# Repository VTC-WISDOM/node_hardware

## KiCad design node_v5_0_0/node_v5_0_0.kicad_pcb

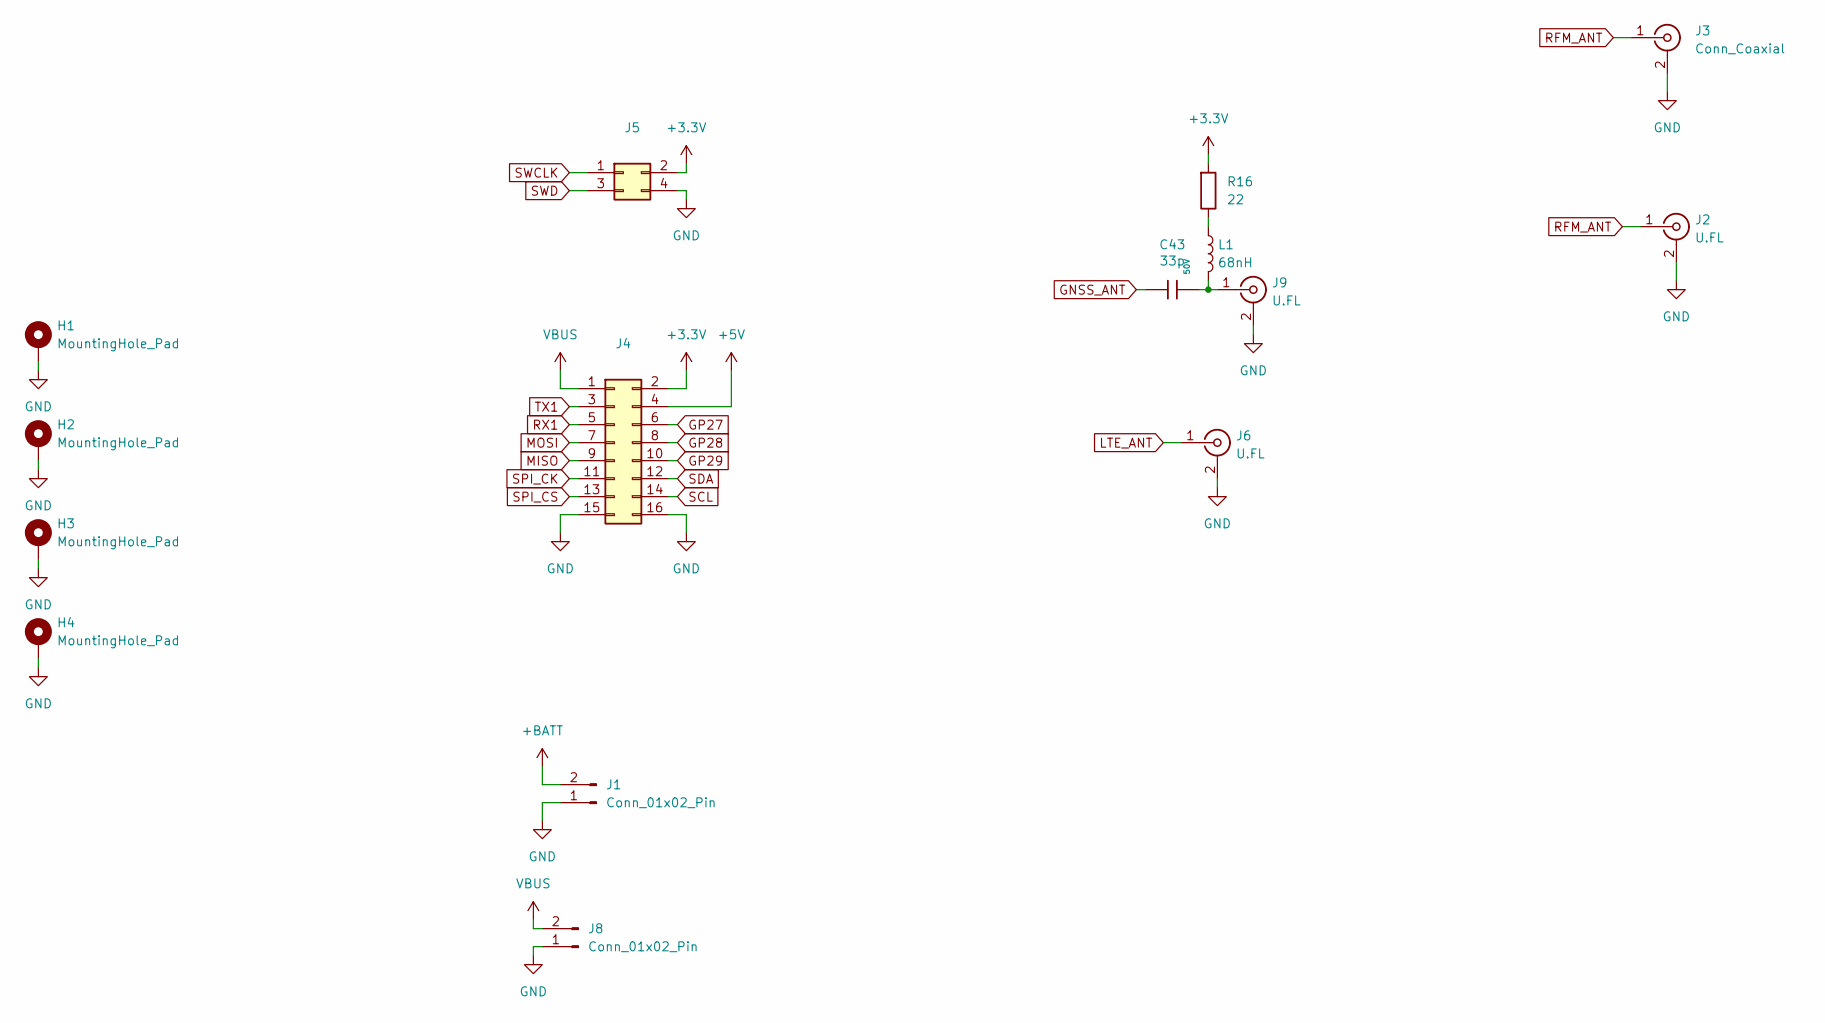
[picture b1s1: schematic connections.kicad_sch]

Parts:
C43: 33p; C_0402; Voltage Rated 50V; Tolerance ±5%; Part 0402CG330J500NT; LCSC C1562
H1, H2, H3, H4: MountingHole_Pad; MountingHole_2.2mm_M2_Pad_TopBottom
J1, J8: Conn_01x02_Pin; JST_PH_B2B-PH-K_1x02_P2.00mm_Vertical
J2, J6, J9: U.FL; IPEX-SMD_BWIPX-1-001E; LCSC C5137195
J3: Conn_Coaxial; SMA_Samtec_SMA-J-P-H-ST-EM1_EdgeMount
J4: Conn_02x08_Odd_Even; PinHeader_2x08_P2.54mm_Vertical
J5: Conn_02x02_Odd_Even; PinHeader_2x02_P2.54mm_Vertical
L1: 68nH; L_0402_1005Metric_Pad0.77x0.64mm_HandSolder
R16: 22; R_0805; Overload Voltage (Max) 150V; Tolerance ±1%; Part 0805W8F220JT5E; LCSC C17561

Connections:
+3.3V: J4.2, J5.2, R16.1; also elsewhere on the board
+5V: J4.4; also elsewhere on the board
+BATT: J1.2; also elsewhere on the board
GND: H1.1, H2.1, H3.1, H4.1, J1.1, J2.2 (Ext), J2.3, J3.2 (Ext), J4.15, J4.16, J5.4, J6.2 (Ext), J6.3, J8.1, J9.2 (Ext), J9.3; also elsewhere on the board
GNSS_ANT: C43.1; also elsewhere on the board
GP27: J4.6; also elsewhere on the board
GP28: J4.8; also elsewhere on the board
GP29: J4.10; also elsewhere on the board
LTE_ANT: J6.1 (In); also elsewhere on the board
MISO: J4.9; also elsewhere on the board
MOSI: J4.7; also elsewhere on the board
unnamed: C43.2, J9.1 (In), L1.2
unnamed: L1.1, R16.2
RFM_ANT: J2.1 (In), J3.1 (In); also elsewhere on the board
RX1: J4.5; also elsewhere on the board
SCL: J4.14; also elsewhere on the board
SDA: J4.12; also elsewhere on the board
SPI_CK: J4.11; also elsewhere on the board
SPI_CS: J4.13; also elsewhere on the board
SWCLK: J5.1; also elsewhere on the board
SWD: J5.3; also elsewhere on the board
TX1: J4.3; also elsewhere on the board
VBUS: J4.1, J8.2; also elsewhere on the board

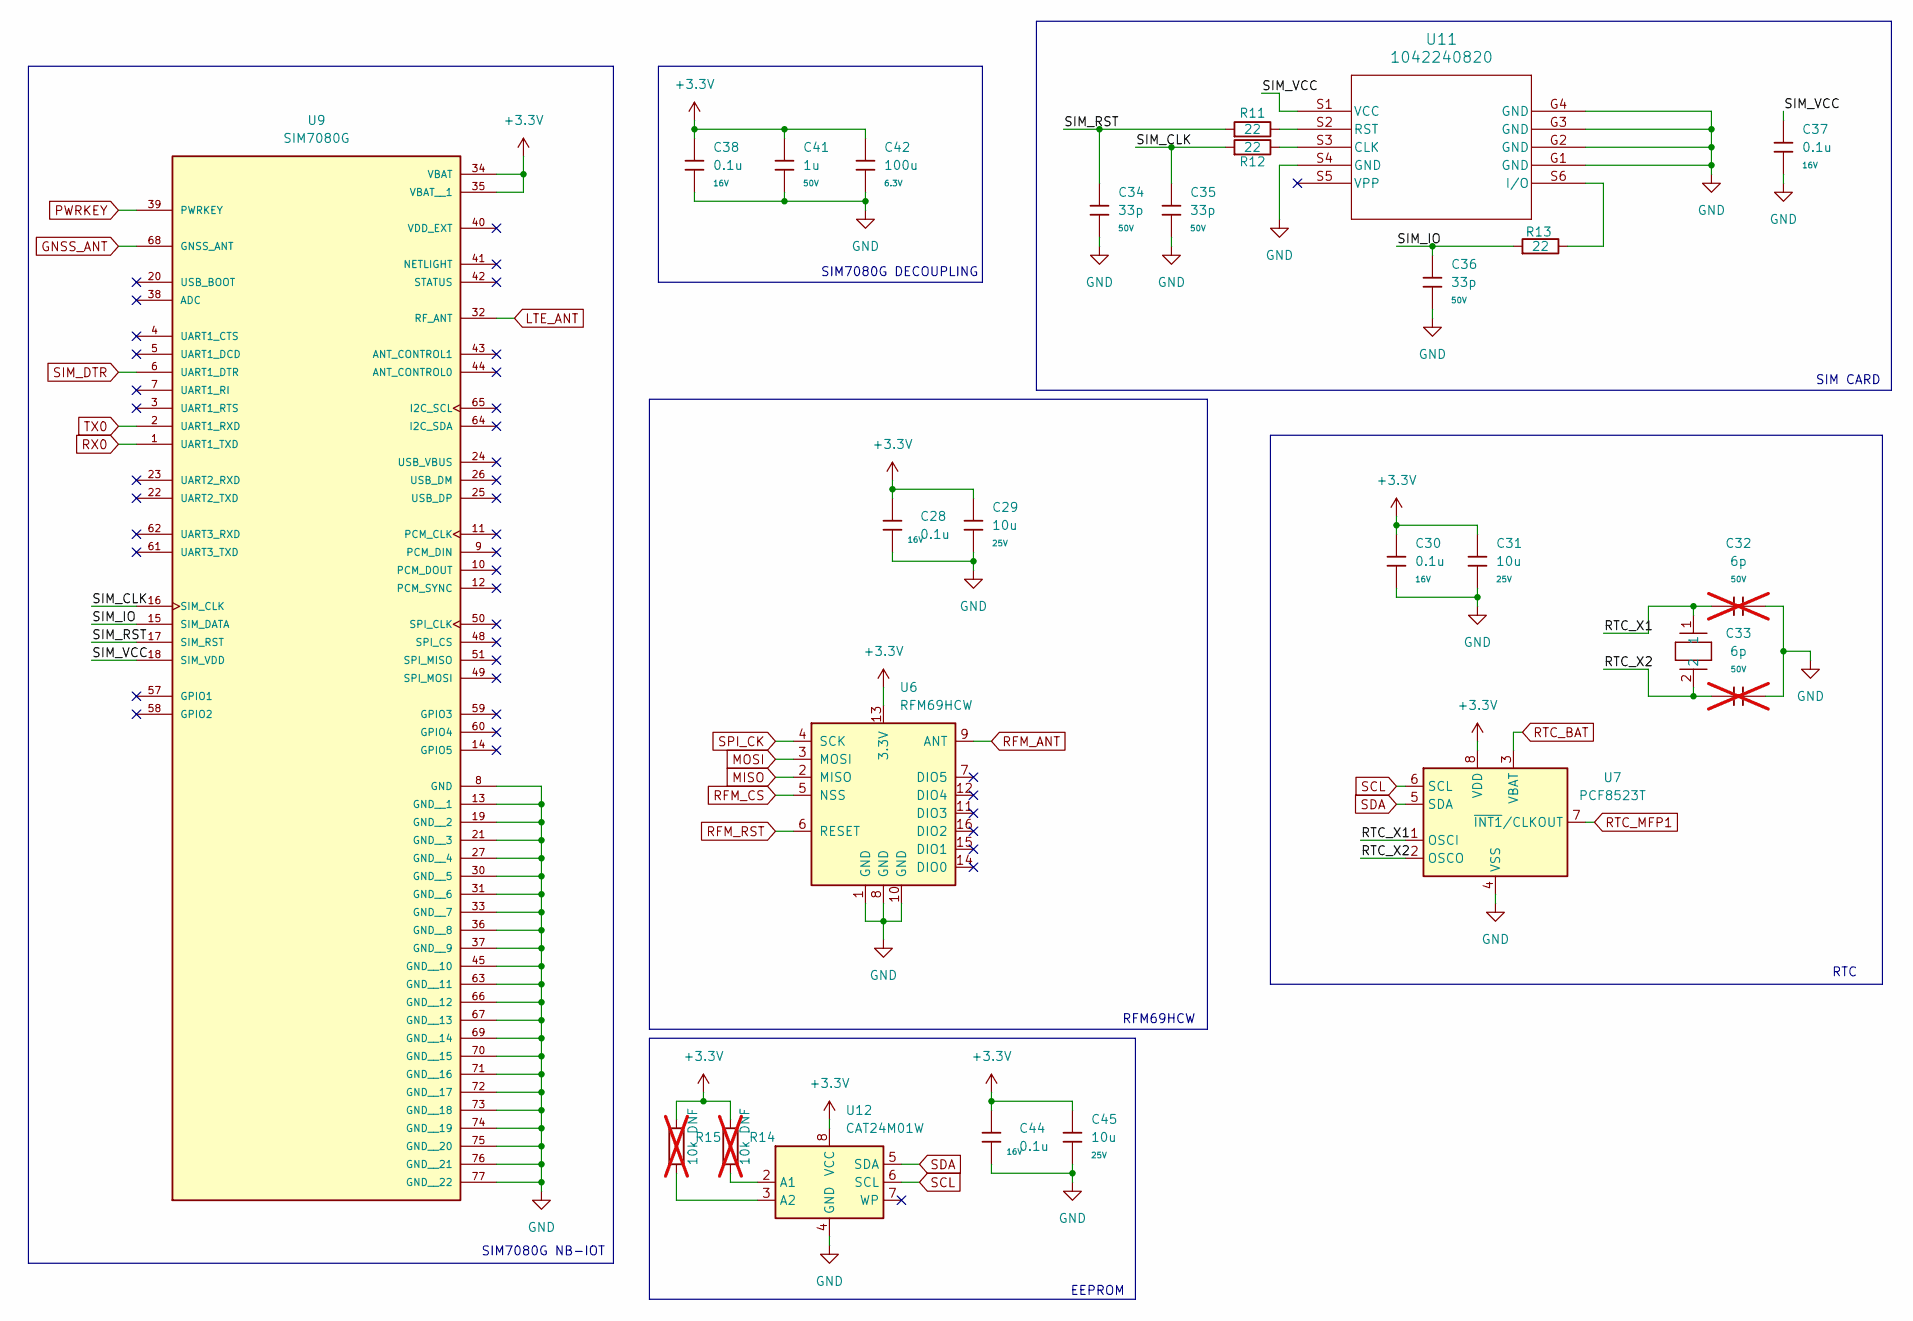
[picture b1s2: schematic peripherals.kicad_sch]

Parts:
C28, C30, C37, C38, C44: 0.1u; C_0402; Voltage Rated 16V; Tolerance ±10%; Part CL05B104KO5NNNC; LCSC C1525
C29, C31, C45: 10u; C_0805; Voltage Rated 25V; Tolerance ±10%; Part CL21A106KAYNNNE; LCSC C15850
C32, C33: 6p; C_0603; Voltage Rated 50V; Part 0603CG6R0C500NT; LCSC C37474; not fitted
C34, C35, C36: 33p; C_0402; Voltage Rated 50V; Tolerance ±5%; Part 0402CG330J500NT; LCSC C1562
C41: 1u; C_0805; Voltage Rated 50V; Tolerance ±10%; Part CL21B105KBFNNNE; LCSC C28323
C42: 100u; C_0805; Voltage Rated 6.3V; Tolerance ±20%; Part CL21A476MQYNNNE; LCSC C16780
R11, R12, R13: 22; R_0805; Overload Voltage (Max) 150V; Tolerance ±1%; Part 0805W8F220JT5E; LCSC C17561
R14, R15: 10k DNF; R_0402_1005Metric_Pad0.72x0.64mm_HandSolder; not fitted
U6: RFM69HCW; HOPERF_RFM9XW_SMD
U7: PCF8523T; SOIC-8_3.9x4.9mm_P1.27mm
U9: SIM7080G; XCVR_SIM7080G; PARTREV 1.04
U11: 1042240820; 1042240820_MOL
U12: CAT24M01W; SOIC-8_3.9x4.9mm_P1.27mm
XTAL1: SC32S-7PF20PPM; XTAL_SC32S-7PF20PPM_EPS

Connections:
+3.3V: C28.1, C29.1, C30.1, C31.1, C38.1, C41.1, C42.1, C44.1, C45.1, R14.1, R15.1, U6.13 (3.3V), U7.8 (VDD), U9.34 (VBAT), U9.35 (VBAT__1), U12.8 (VCC); also elsewhere on the board
/PERIPHERALS/RTC_X1: C32.1, U7.1 (OSCI), XTAL1.1
/PERIPHERALS/RTC_X2: C33.1, U7.2 (OSCO), XTAL1.2
/PERIPHERALS/SIM_CLK: C35.1, R12.1, U9.16 (SIM_CLK)
/PERIPHERALS/SIM_IO: C36.1, R13.1, U9.15 (SIM_DATA)
/PERIPHERALS/SIM_RST: C34.1, R11.1, U9.17 (SIM_RST)
/PERIPHERALS/SIM_VCC: C37.1, U9.18 (SIM_VDD), U11.S1 (VCC)
GND: C28.2, C29.2, C30.2, C31.2, C32.2, C33.2, C34.2, C35.2, C36.2, C37.2, C38.2, C41.2, C42.2, C44.2, C45.2, U6.1 (GND), U6.8 (GND), U6.10 (GND), U7.4 (VSS), U9.8 (GND), U9.13 (GND__1), U9.19 (GND__2), U9.21 (GND__3), U9.27 (GND__4), U9.30 (GND__5), U9.31 (GND__6), U9.33 (GND__7), U9.36 (GND__8), U9.37 (GND__9), U9.45 (GND__10), U9.63 (GND__11), U9.66 (GND__12), U9.67 (GND__13), U9.69 (GND__14), U9.70 (GND__15), U9.71 (GND__16), U9.72 (GND__17), U9.73 (GND__18), U9.74 (GND__19), U9.75 (GND__20), U9.76 (GND__21), U9.77 (GND__22), U11.11, U11.12, U11.G1 (GND), U11.G2 (GND), U11.G3 (GND), U11.G4 (GND), U11.S4 (GND), U12.4 (GND); also elsewhere on the board
GNSS_ANT: U9.68 (GNSS_ANT); also elsewhere on the board
LTE_ANT: U9.32 (RF_ANT); also elsewhere on the board
MISO: U6.2 (MISO); also elsewhere on the board
MOSI: U6.3 (MOSI); also elsewhere on the board
unnamed 34: U7.3 (VBAT); also elsewhere on the board
unnamed: R12.2, U11.S3 (CLK)
unnamed: R13.2, U11.S6 (I/O)
unnamed: R11.2, U11.S2 (RST)
unnamed: R14.2, U12.2 (A1)
unnamed: R15.2, U12.3 (A2)
PWRKEY: U9.39 (PWRKEY); also elsewhere on the board
RFM_ANT: U6.9 (ANT); also elsewhere on the board
RFM_CS: U6.5 (NSS); also elsewhere on the board
RFM_DIO0: U6.14 (DIO0); also elsewhere on the board
RFM_DIO1: U6.15 (DIO1); also elsewhere on the board
RFM_DIO2: U6.16 (DIO2); also elsewhere on the board
RFM_DIO3: U6.11 (DIO3); also elsewhere on the board
RFM_DIO4: U6.12 (DIO4); also elsewhere on the board
RFM_DIO5: U6.7 (DIO5); also elsewhere on the board
RFM_RST: U6.6 (RESET); also elsewhere on the board
RTC_MFP1: U7.7 (~INT1/CLKOUT); also elsewhere on the board
RX0: U9.1 (UART1_TXD); also elsewhere on the board
SCL: U7.6 (SCL), U12.6 (SCL); also elsewhere on the board
SDA: U7.5 (SDA), U12.5 (SDA); also elsewhere on the board
SIM_DTR: U9.6 (UART1_DTR); also elsewhere on the board
SPI_CK: U6.4 (SCK); also elsewhere on the board
TX0: U9.2 (UART1_RXD); also elsewhere on the board

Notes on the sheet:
RFM69HCW
EEPROM
SIM7080G DECOUPLING
RTC
SIM CARD
SIM7080G NB-IOT

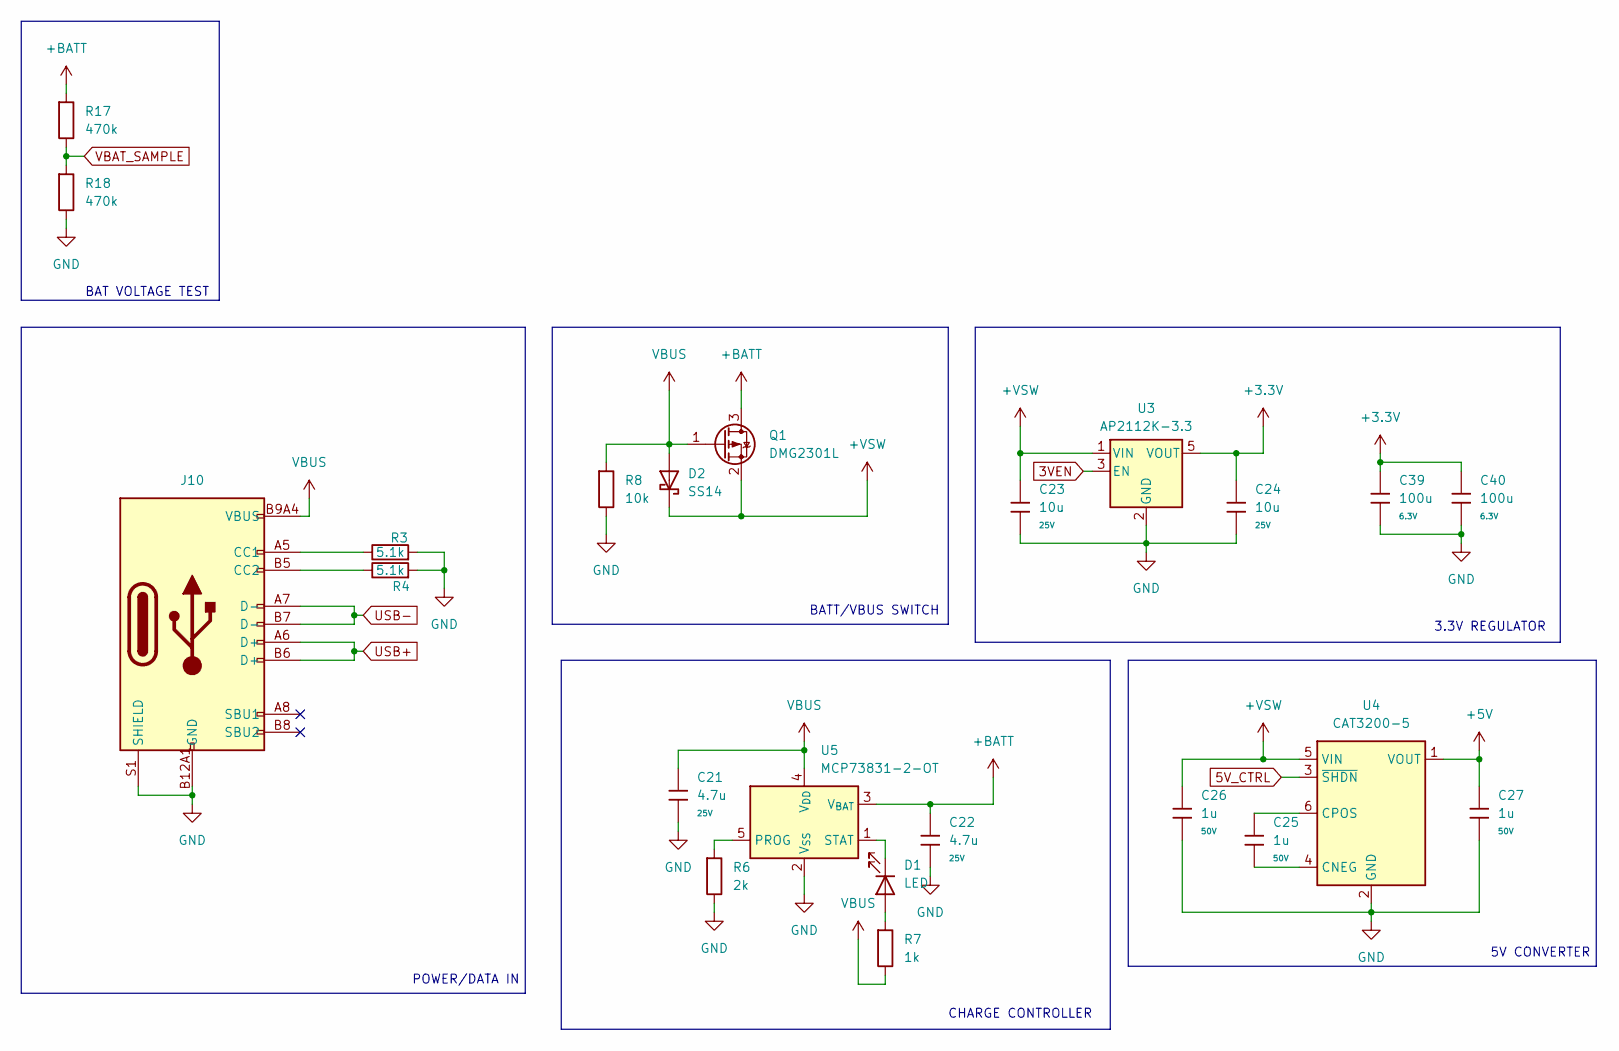
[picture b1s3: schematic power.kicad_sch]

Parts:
C21, C22: 4.7u; C_0805; Voltage Rated 25V; Tolerance ±10%; Part CL21A475KAQNNNE; LCSC C1779
C23, C24: 10u; C_0805; Voltage Rated 25V; Tolerance ±10%; Part CL21A106KAYNNNE; LCSC C15850
C25, C26, C27: 1u; C_0805; Voltage Rated 50V; Tolerance ±10%; Part CL21B105KBFNNNE; LCSC C28323
C39, C40: 100u; C_0805; Voltage Rated 6.3V; Tolerance ±20%; Part CL21A476MQYNNNE; LCSC C16780
D1: LED; LED_1206_3216Metric_Pad1.42x1.75mm_HandSolder
D2: SS14; D_SMA; Forward Voltage (Vf@If) 550mV@1A; Reverse Voltage (Vr) 40V; Part SS14; LCSC C2480
J10: Connector, USB-TYPE-C-16P; TYPE-C-SMD_HX-TYPE-C-16PIN; LCSC C2927039
Q1: DMG2301L; SOT-23
R3, R4: 5.1k; R_0805_2012Metric_Pad1.20x1.40mm_HandSolder
R6: 2k; R_0805; Overload Voltage (Max) 150V; Tolerance ±1%; Part 0805W8F2001T5E; LCSC C17604
R7: 1k; R_0805; Overload Voltage (Max) 150V; Tolerance ±1%; Part 0805W8F1001T5E; LCSC C17513
R8: 10k; R_0805; Overload Voltage (Max) 150V; Tolerance ±1%; Part 0805W8F1002T5E; LCSC C17414
R17, R18: 470k; R_0805; Overload Voltage (Max) 150V; Tolerance ±1%; Part 0805W8F4703T5E; LCSC C17709
U3: AP2112K-3.3; SOT-23-5
U4: CAT3200-5; SOT-23-6
U5: MCP73831-2-OT; SOT-23-5

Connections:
3VEN: U3.3 (EN); also elsewhere on the board
5V_CTRL: U4.3 (~SHDN); also elsewhere on the board
+3.3V: C24.1, C39.1, C40.1, U3.5 (VOUT); also elsewhere on the board
+5V: C27.1, U4.1 (VOUT); also elsewhere on the board
+BATT: C22.1, Q1.3 (D), R17.1, U5.3 (V_{BAT}); also elsewhere on the board
+VSW: C23.1, C26.1, D2.1, Q1.2 (S), U3.1 (VIN), U4.5 (VIN); also elsewhere on the board
GND: C21.2, C22.2, C23.2, C24.2, C26.2, C27.2, C39.2, C40.2, J10.A12B1 (GND), J10.B12A1 (GND), J10.S1 (SHIELD), R3.2, R4.2, R6.2, R8.2, R18.2, U3.2 (GND), U4.2 (GND), U5.2 (V_{SS}); also elsewhere on the board
unnamed: D1.2 (A), R7.1
unnamed: D1.1 (K), U5.1 (STAT)
unnamed: J10.A5 (CC1), R3.1
unnamed: J10.B5 (CC2), R4.1
unnamed: C25.2, U4.4 (CNEG)
unnamed: C25.1, U4.6 (CPOS)
unnamed: R6.1, U5.5 (PROG)
VBAT_SAMPLE: R17.2, R18.1; also elsewhere on the board
VBUS: C21.1, D2.2, J10.A9B4 (VBUS), J10.B9A4 (VBUS), Q1.1 (G), R7.2, R8.1, U5.4 (V_{DD}); also elsewhere on the board

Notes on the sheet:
POWER/DATA IN
BATT/VBUS SWITCH
5V CONVERTER
BAT VOLTAGE TEST
3.3V REGULATOR
CHARGE CONTROLLER

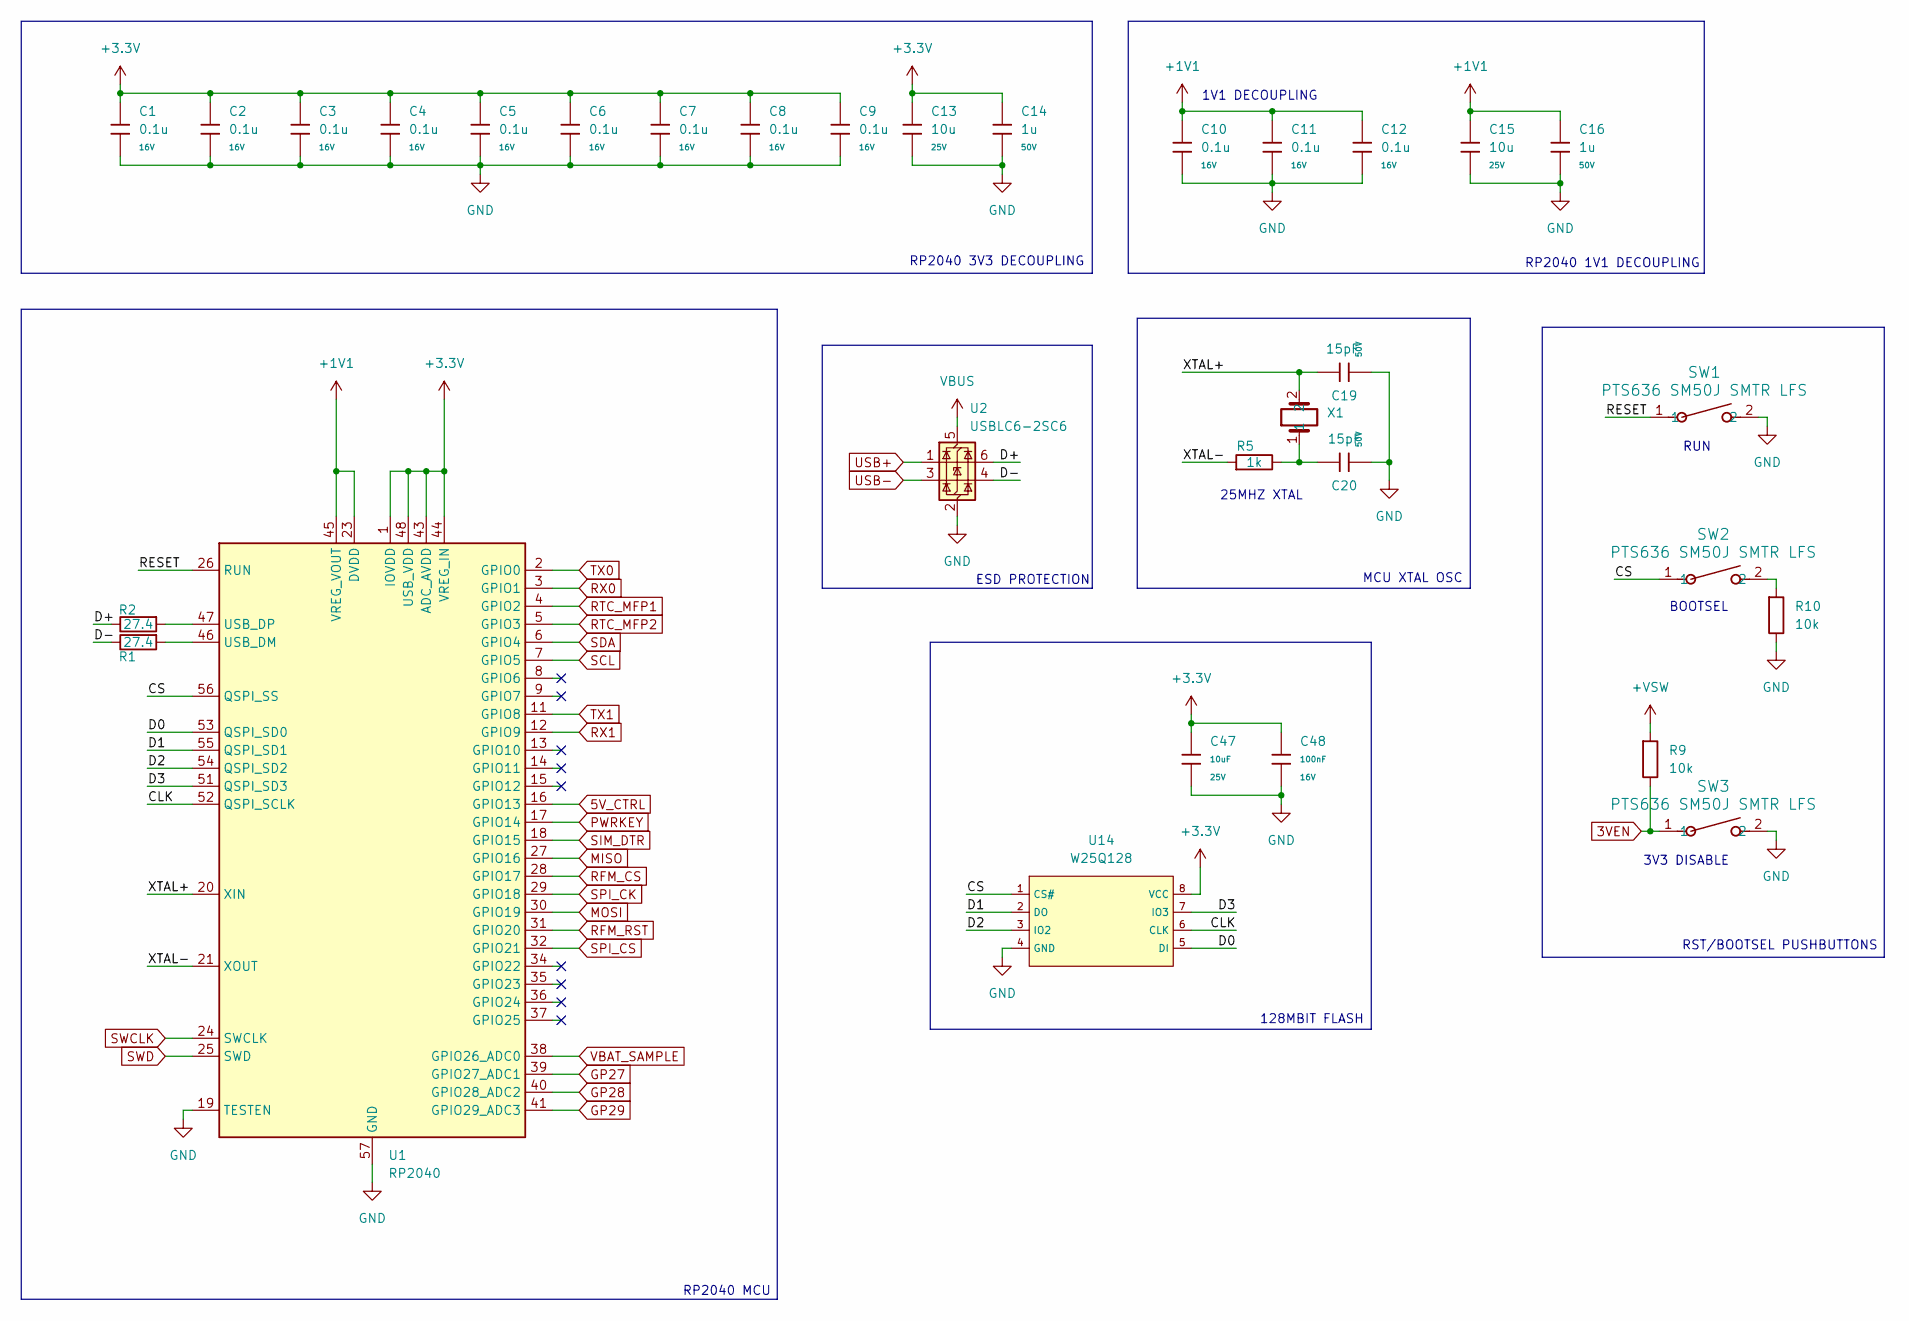
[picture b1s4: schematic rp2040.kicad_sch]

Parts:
C1, C2, C3, C4, C5, C6, C7, C8, C9, C10, C11, C12: 0.1u; C_0402; Voltage Rated 16V; Tolerance ±10%; Part CL05B104KO5NNNC; LCSC C1525
C13, C15: 10u; C_0805; Voltage Rated 25V; Tolerance ±10%; Part CL21A106KAYNNNE; LCSC C15850
C14, C16: 1u; C_0805; Voltage Rated 50V; Tolerance ±10%; Part CL21B105KBFNNNE; LCSC C28323
C19, C20: 15pF; C_0402; Voltage Rated 50V; Tolerance ±5%; Part 0402CG150J500NT; LCSC C1548
C47: 10uF; C_0805; Voltage Rated 25V; Tolerance ±10%; Part CL21A106KAYNNNE; LCSC C15850
C48: 100nF; C_0402; Voltage Rated 16V; Tolerance ±10%; Part CL05B104KO5NNNC; LCSC C1525
R1, R2: 27.4; R_0603; Overload Voltage (Max) 75V; Tolerance ±1%; Part 0603WAF270JT5E; LCSC C25190
R5: 1k; R_0805; Overload Voltage (Max) 150V; Tolerance ±1%; Part 0805W8F1001T5E; LCSC C17513
R9, R10: 10k; R_0805; Overload Voltage (Max) 150V; Tolerance ±1%; Part 0805W8F1002T5E; LCSC C17414
SW1, SW2, SW3: PTS636 SM50J SMTR LFS; SW_PTS636_CNK
U1: RP2040; QFN-56-1EP_7x7mm_P0.4mm_EP3.2x3.2mm_ThermalVias; LCSC C2040
U2: USBLC6-2SC6; SOT-23-6
U14: W25Q128; SOIC-8_L5.3-W5.3-P1.27-LS8.0-BL; Part W25Q128JVSIQ; LCSC C97521
X1: XTAL-445

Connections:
3VEN: R9.2, SW3.1; also elsewhere on the board
5V_CTRL: U1.16 (GPIO13); also elsewhere on the board
485_!RE: U1.9 (GPIO7); also elsewhere on the board
485_DE: U1.8 (GPIO6); also elsewhere on the board
+1V1: C10.1, C11.1, C12.1, C15.1, C16.1, U1.23 (DVDD), U1.45 (VREG_VOUT), U1.50 (DVDD)
+3.3V: C1.1, C2.1, C3.1, C4.1, C5.1, C6.1, C7.1, C8.1, C9.1, C13.1, C14.1, C47.1, C48.1, U1.1 (IOVDD), U1.10 (IOVDD), U1.22 (IOVDD), U1.33 (IOVDD), U1.42 (IOVDD), U1.43 (ADC_AVDD), U1.44 (VREG_IN), U1.48 (USB_VDD), U1.49 (IOVDD), U14.8 (VCC); also elsewhere on the board
+VSW: R9.1; also elsewhere on the board
/MCU/CLK: U1.52 (QSPI_SCLK), U14.6 (CLK)
/MCU/CS: SW2.1, U1.56 (QSPI_SS), U14.1 (CS#)
/MCU/D0: U1.53 (QSPI_SD0), U14.5 (DI)
/MCU/D1: U1.55 (QSPI_SD1), U14.2 (DO)
/MCU/D2: U1.54 (QSPI_SD2), U14.3 (IO2)
/MCU/D3: U1.51 (QSPI_SD3), U14.7 (IO3)
/MCU/RESET: SW1.1, U1.26 (RUN)
/MCU/XTAL+: C19.1, U1.20 (XIN), X1.2
/MCU/XTAL-: R5.1, U1.21 (XOUT)
GND: C1.2, C2.2, C3.2, C4.2, C5.2, C6.2, C7.2, C8.2, C9.2, C10.2, C11.2, C12.2, C13.2, C14.2, C15.2, C16.2, C19.2, C20.2, C47.2, C48.2, R10.2, SW1.2, SW3.2, U1.19 (TESTEN), U1.57 (GND), U2.2 (GND), U14.4 (GND); also elsewhere on the board
GP27: U1.39 (GPIO27_ADC1); also elsewhere on the board
GP28: U1.40 (GPIO28_ADC2); also elsewhere on the board
GP29: U1.41 (GPIO29_ADC3); also elsewhere on the board
MISO: U1.27 (GPIO16); also elsewhere on the board
MOSI: U1.30 (GPIO19); also elsewhere on the board
unnamed: C20.1, R5.2, X1.1
unnamed: R10.1, SW2.2
unnamed: R1.1, U1.46 (USB_DM)
unnamed: R2.1, U1.47 (USB_DP)
PWRKEY: U1.17 (GPIO14); also elsewhere on the board
RFM_CS: U1.28 (GPIO17); also elsewhere on the board
RFM_DIO0: U1.13 (GPIO10); also elsewhere on the board
RFM_DIO1: U1.14 (GPIO11); also elsewhere on the board
RFM_DIO2: U1.34 (GPIO22); also elsewhere on the board
RFM_DIO3: U1.35 (GPIO23); also elsewhere on the board
RFM_DIO4: U1.36 (GPIO24); also elsewhere on the board
RFM_DIO5: U1.37 (GPIO25); also elsewhere on the board
RFM_RST: U1.31 (GPIO20); also elsewhere on the board
RTC_MFP1: U1.4 (GPIO2); also elsewhere on the board
RTC_MFP2: U1.5 (GPIO3)
RX0: U1.3 (GPIO1); also elsewhere on the board
RX1: U1.12 (GPIO9); also elsewhere on the board
SCL: U1.7 (GPIO5); also elsewhere on the board
SDA: U1.6 (GPIO4); also elsewhere on the board
SIM_DTR: U1.18 (GPIO15); also elsewhere on the board
SPI_CK: U1.29 (GPIO18); also elsewhere on the board
SPI_CS: U1.32 (GPIO21); also elsewhere on the board
SWCLK: U1.24 (SWCLK); also elsewhere on the board
SWD: U1.25 (SWD); also elsewhere on the board
TX0: U1.2 (GPIO0); also elsewhere on the board
TX1: U1.11 (GPIO8); also elsewhere on the board
VBAT_SAMPLE: U1.38 (GPIO26_ADC0); also elsewhere on the board
VBUS: U2.5 (VBUS); also elsewhere on the board

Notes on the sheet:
RST/BOOTSEL PUSHBUTTONS
RP2040 3V3 DECOUPLING
RP2040 MCU
RUN
RP2040 1V1 DECOUPLING
BOOTSEL
3V3 DISABLE
MCU XTAL OSC
1V1 DECOUPLING
25MHZ XTAL
128MBIT FLASH
ESD PROTECTION

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
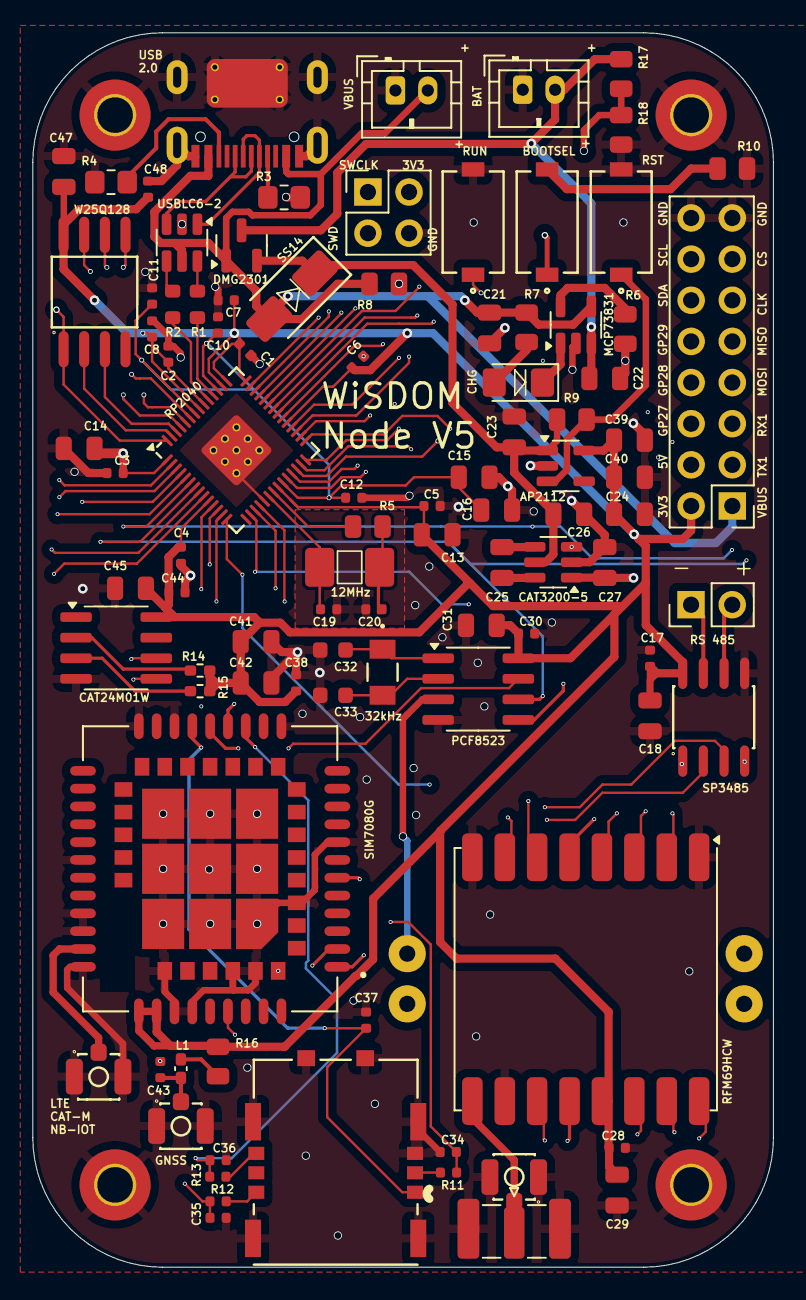
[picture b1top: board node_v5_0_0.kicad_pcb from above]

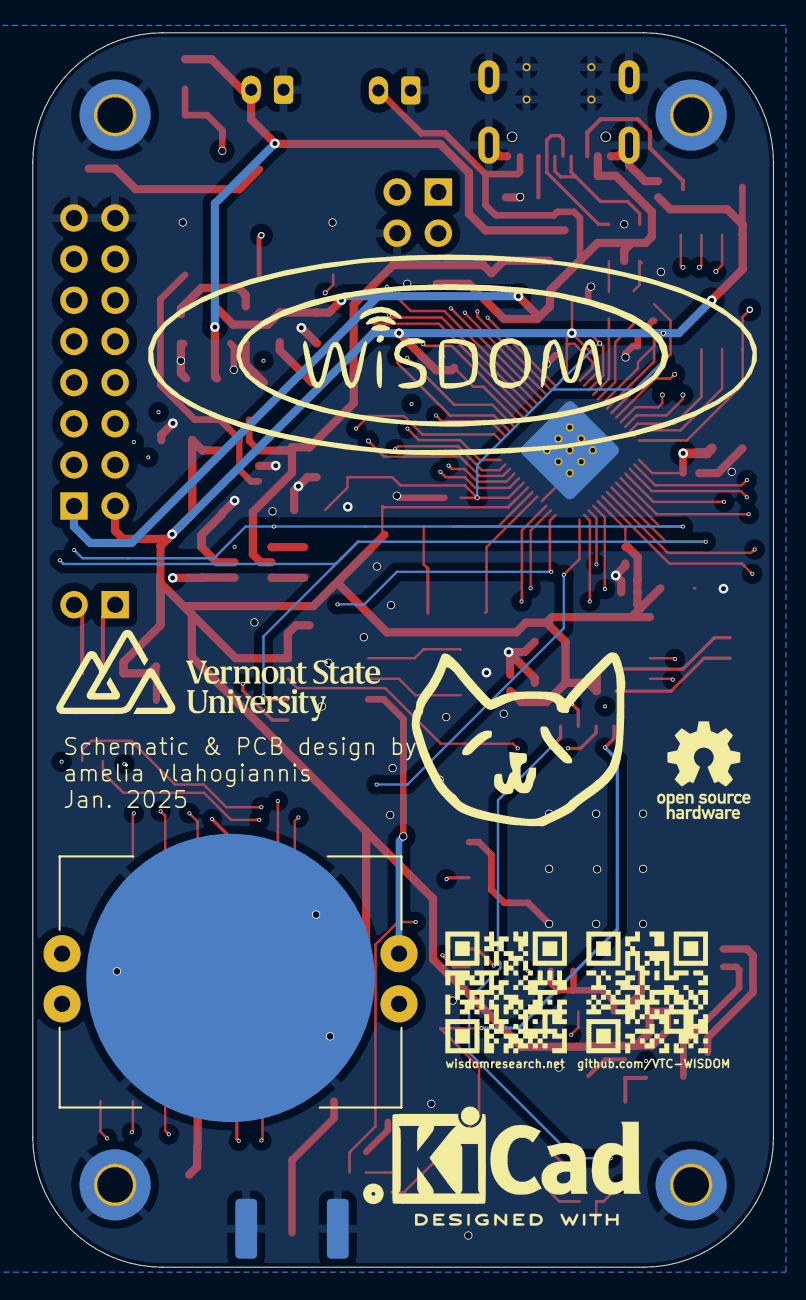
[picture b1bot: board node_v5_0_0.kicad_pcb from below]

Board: 4 copper layers, 45.7 x 76.2 mm, 102 parts (3 on the bottom side), 81 nets.

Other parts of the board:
BT1: Battery_Cell; BAT_BAT-HLD-001-THM
C17: 0.1u; C_0402
C18: 10u; C_0805
J7: Conn_01x02_Pin; PinHeader_1x02_P2.54mm_Vertical
LOGO: github_qr
LOGO#2: qrcode
U8: SP3485EN; SOIC-8_L5.0-W4.0-P1.27-LS6.0-BL

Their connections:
485+: J7.2, U8.6 (A)
485-: J7.1, U8.7 (B)
485_!RE: U8.2 (RE#); also elsewhere on the board
485_DE: U8.3 (DE); also elsewhere on the board
+3.3V: C17.1, C18.1, U8.8 (VCC); also elsewhere on the board
GND: BT1.2 (-), C17.2, C18.2, U8.5 (GND); also elsewhere on the board
unnamed 34: BT1.1 (+); also elsewhere on the board
RX1: U8.1 (RO); also elsewhere on the board
TX1: U8.4 (DI); also elsewhere on the board
